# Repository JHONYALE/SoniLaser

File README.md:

# SoniLaser
En este repositorio se encuentra el proceso de desarrollo documentado del Proyecto Taller de Ingeniería Electrónica

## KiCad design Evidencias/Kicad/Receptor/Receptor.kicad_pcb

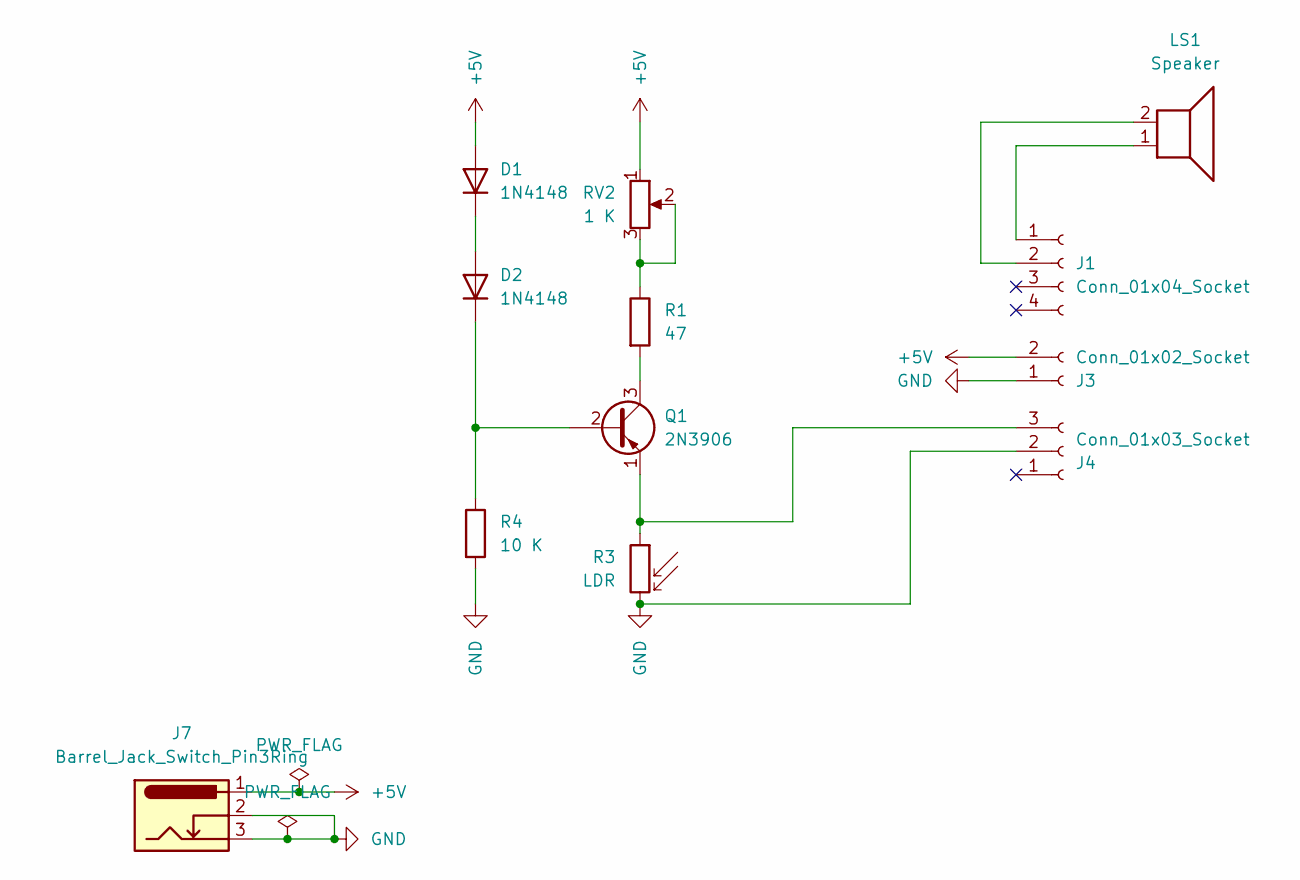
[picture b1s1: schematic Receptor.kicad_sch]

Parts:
D1, D2: 1N4148; D_DO-35_SOD27_P7.62mm_Horizontal
J1: Conn_01x04_Socket; PinSocket_1x04_P2.54mm_Vertical
J3: Conn_01x02_Socket; PinSocket_1x02_P2.54mm_Vertical
J4: Conn_01x03_Socket; PinSocket_1x03_P2.54mm_Vertical
J7: Barrel_Jack_Switch_Pin3Ring; BarrelJack_Horizontal
LS1: Speaker; PinHeader_1x02_P2.54mm_Vertical
Q1: 2N3906; TO-92_Inline
R1: 47; R_Axial_DIN0411_L9.9mm_D3.6mm_P15.24mm_Horizontal
R3: LDR; R_LDR_10x8.5mm_P7.6mm_Vertical
R4: 10 K; R_Axial_DIN0411_L9.9mm_D3.6mm_P15.24mm_Horizontal
RV2: 1 K; Potentiometer_Piher_T-16H_Single_Horizontal

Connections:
+5V: D1.2 (A), J3.2, J7.1, RV2.1
GND: J3.1, J4.2, J7.2, J7.3, R3.2, R4.2
unnamed: D1.1 (K), D2.2 (A)
unnamed: D2.1 (K), Q1.2 (B), R4.1
unnamed: J1.1, LS1.1
unnamed: J1.2, LS1.2
unnamed: J4.3, Q1.1 (E), R3.1
unnamed: Q1.3 (C), R1.2
unnamed: R1.1, RV2.2, RV2.3

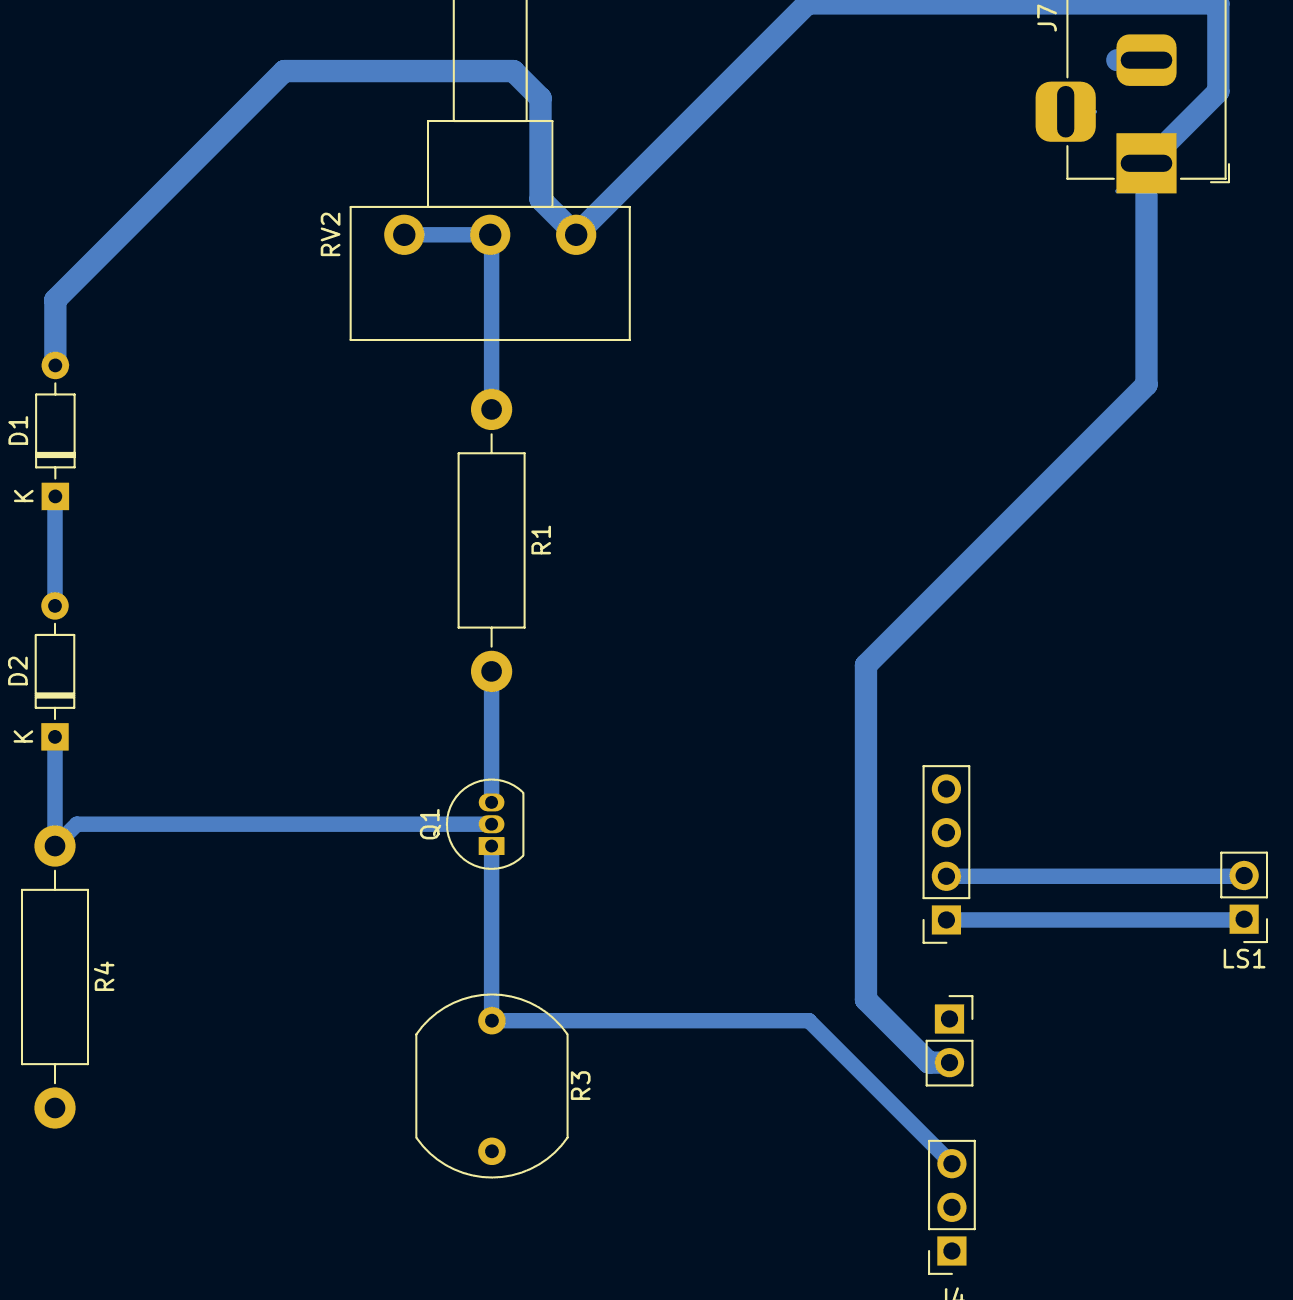
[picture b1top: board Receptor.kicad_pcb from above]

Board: 2 copper layers, 12 parts (0 on the bottom side), 9 nets.

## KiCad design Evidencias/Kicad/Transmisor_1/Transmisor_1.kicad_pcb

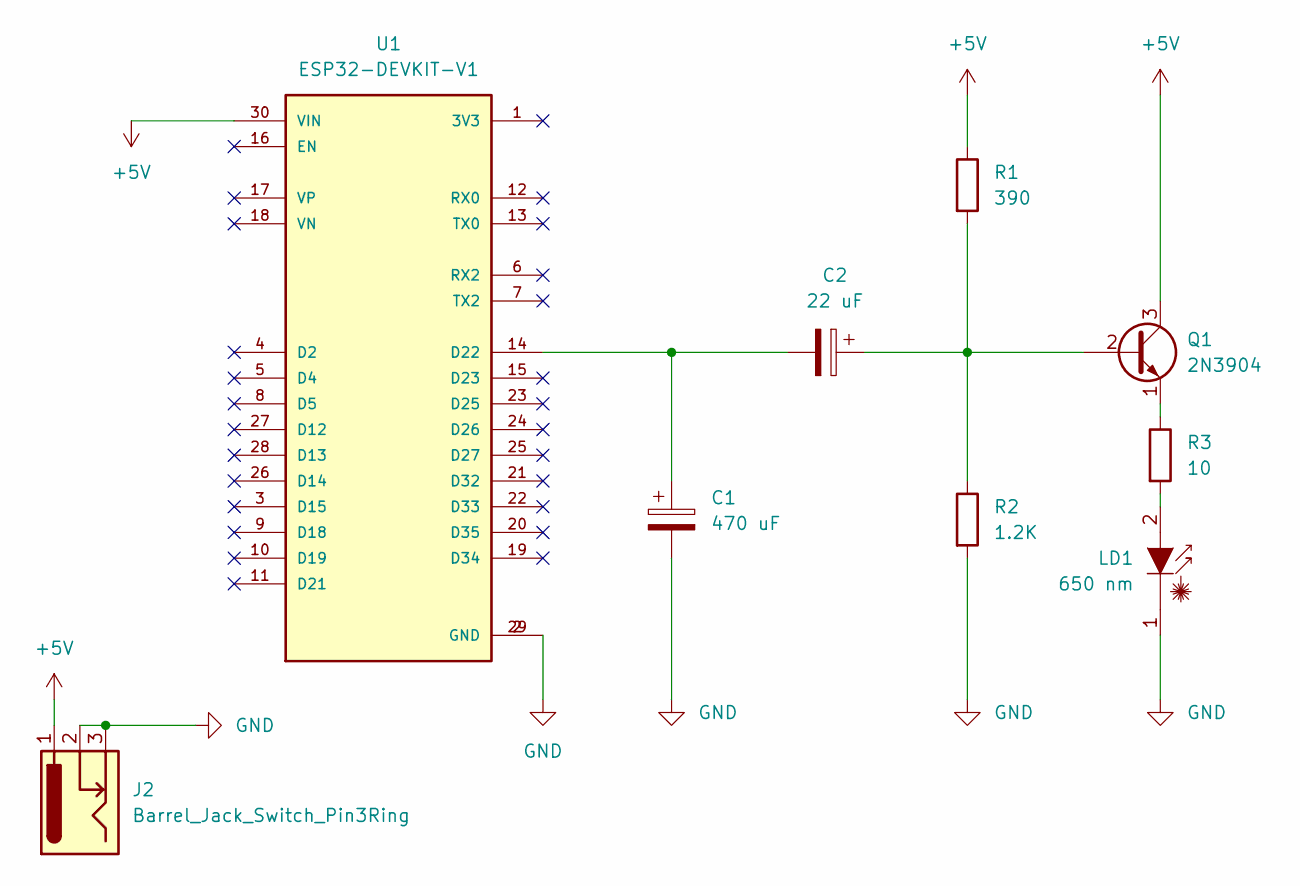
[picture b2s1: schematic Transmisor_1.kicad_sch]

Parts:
C1: 470 uF; CP_Radial_D10.0mm_P3.50mm
C2: 22 uF; CP_Radial_D10.0mm_P3.50mm
J2: Barrel_Jack_Switch_Pin3Ring; BarrelJack_GCT_DCJ200-10-A_Horizontal
LD1: 650 nm; LED_D5.0mm
Q1: 2N3904; TO-92_Inline
R1: 390; R_Axial_DIN0411_L9.9mm_D3.6mm_P15.24mm_Horizontal
R2: 1.2K; R_Axial_DIN0411_L9.9mm_D3.6mm_P15.24mm_Horizontal
R3: 10; R_Axial_DIN0411_L9.9mm_D3.6mm_P15.24mm_Horizontal
U1: ESP32-DEVKIT-V1; esp32_devkit_v1_doit; PARTREV N/A

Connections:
+5V: J2.1, Q1.3 (C), R1.1, U1.30 (VIN)
GND: C1.2, J2.2, J2.3, LD1.1 (C), R2.2, U1.2 (GND), U1.29 (GND)
unnamed: LD1.2 (A), R3.2
unnamed: C2.1, Q1.2 (B), R1.2, R2.1
unnamed: Q1.1 (E), R3.1
unnamed: C1.1, C2.2, U1.14 (D22)

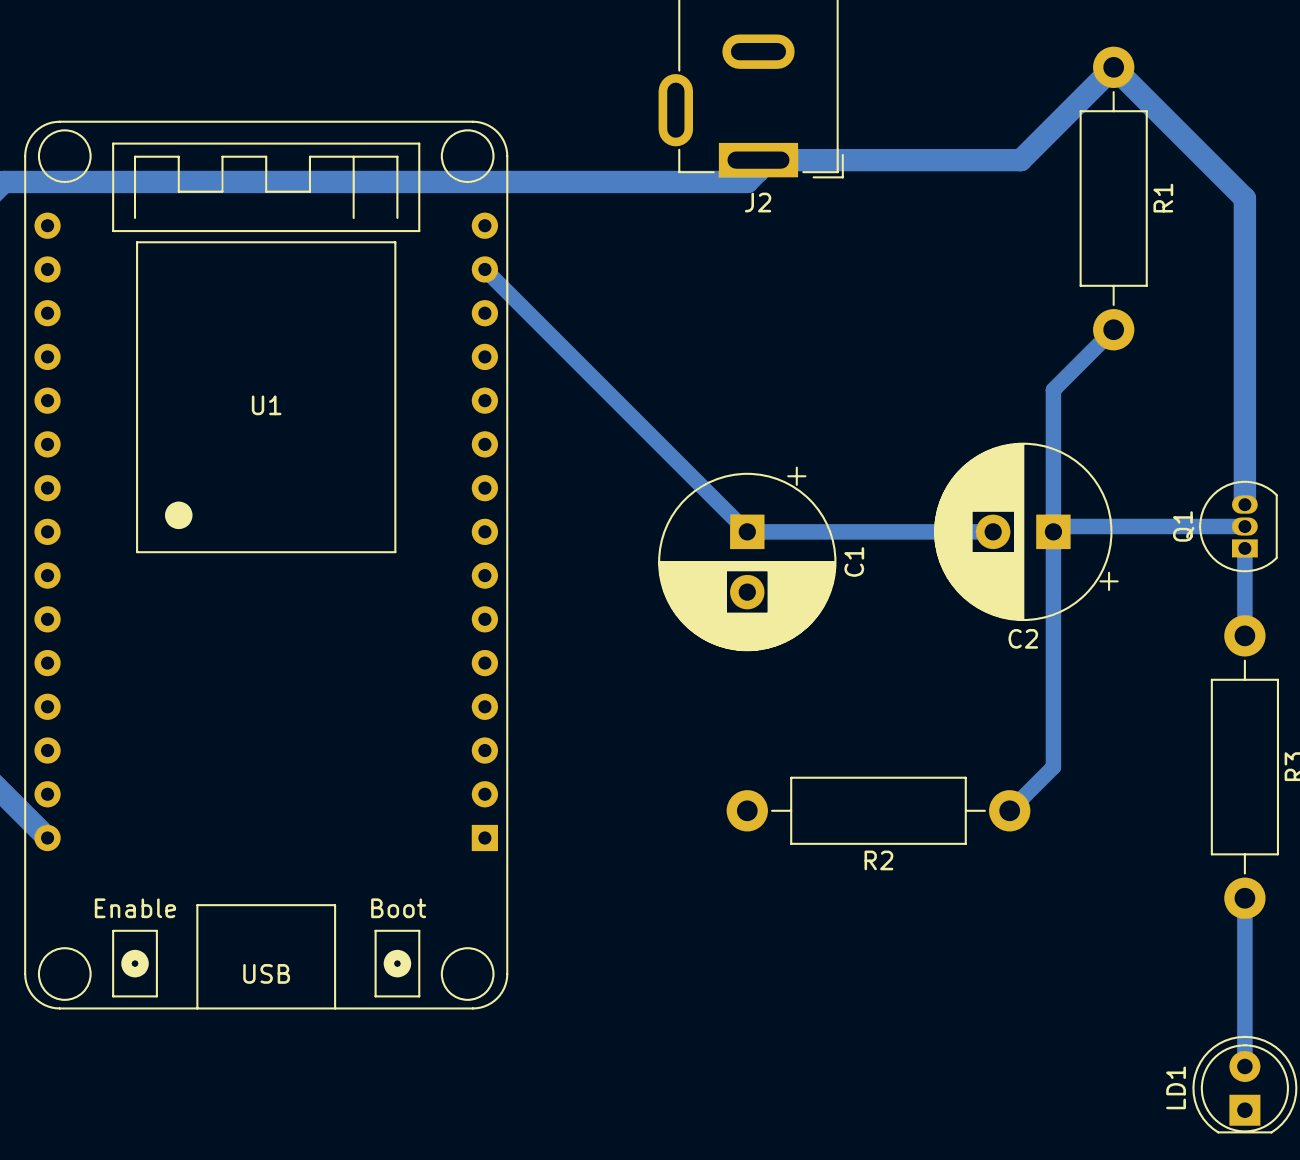
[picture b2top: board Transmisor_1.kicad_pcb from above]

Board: 2 copper layers, 9 parts (0 on the bottom side), 6 nets.

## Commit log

2023-11-30 Create Evidencias
2023-11-30 Rename README.md to Presentación.md
2023-11-30 Rename Presentación.md to REDME.md
2023-11-30 Rename REDME.md to README.md
2023-11-30 Create Código
2023-11-30 Update Código
2023-12-01 Rename Código to Código.py
